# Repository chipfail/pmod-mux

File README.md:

# MUX PMOD Hardware
MUX PMOD Hardware

[Digikey Cart for 10 boards](https://www.digikey.com/short/pm0rpt)

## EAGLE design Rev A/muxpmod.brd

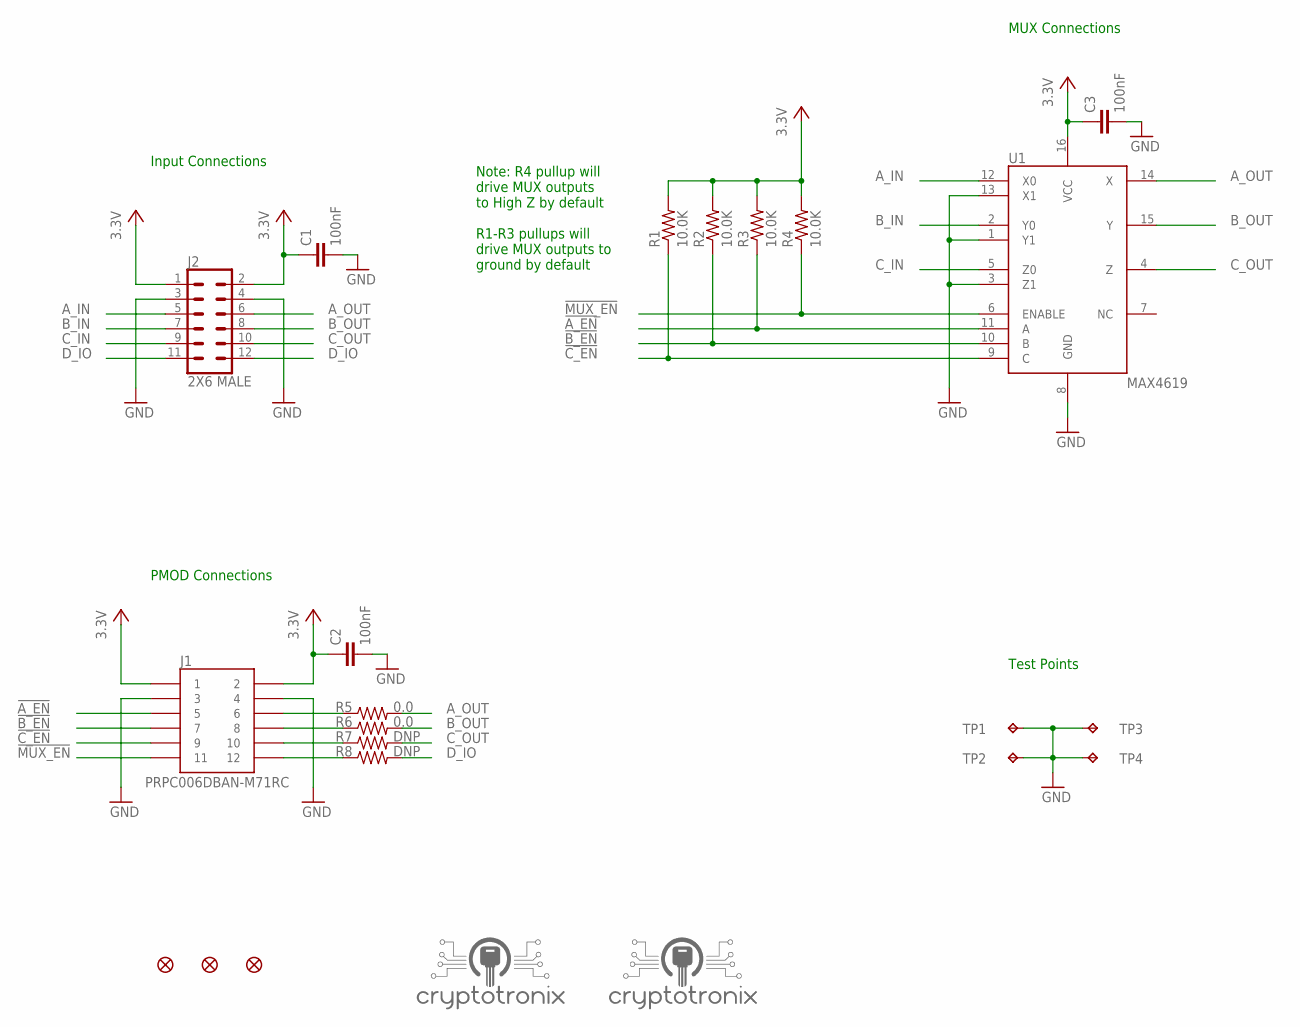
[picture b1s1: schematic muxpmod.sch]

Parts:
C1, C2, C3: 100nF; C0603
FD1, FD2, FD3: FIDUCIALUFIDUCIAL; MICRO-FIDUCIAL
J1: PRPC006DBAN-M71RC
J2: 2X6 MALE; 2X6
LOGO1, LOGO2: CRYPTOTRONIX_LOGO_S
R1, R2, R3, R4: 10.0K; R0603
R5, R6: 0.0; R0603
R7, R8: DNP; R0603
TP1, TP2, TP3, TP4: TEST-POINT-SM; 5015
U1: MAX4619; 16SOIC

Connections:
0V: C1.2, C2.2, C3.2, J1.3, J1.4, J2.3, J2.4, TP1.1, TP2.1, TP3.1, TP4.1, U1.1 (Y1), U1.3 (Z1), U1.8 (GND), U1.13 (X1)
3.3V: C1.1, C2.1, C3.1, J1.1, J1.2, J2.1, J2.2, R1.2, R2.2, R3.2, R4.2, U1.16 (VCC)
!A_EN: J1.5, R3.1, U1.11 (A)
!B_EN: J1.7, R2.1, U1.10 (B)
!C_EN: J1.9, R1.1, U1.9 (C)
!MUX_EN: J1.11, R4.1, U1.6 (ENABLE)
A_IN: J2.5, U1.12 (X0)
A_OUT: J2.6, R5.2, U1.14 (X)
B_IN: J2.7, U1.2 (Y0)
B_OUT: J2.8, R6.2, U1.15 (Y)
C_IN: J2.9, U1.5 (Z0)
C_OUT: J2.10, R7.2, U1.4 (Z)
D_IO: J2.11, J2.12, R8.2
unnamed: J1.6, R5.1
unnamed: J1.8, R6.1
unnamed: J1.10, R7.1
unnamed: J1.12, R8.1

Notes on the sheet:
PMOD Connections
MUX Connections
Note: R4 pullup will drive MUX outputs to High Z by default R1-R3 pullups will drive MUX outputs to ground by default
Test Points
Input Connections

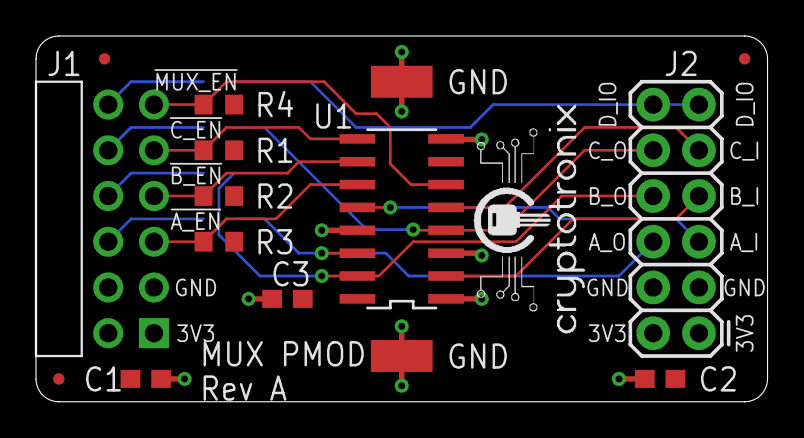
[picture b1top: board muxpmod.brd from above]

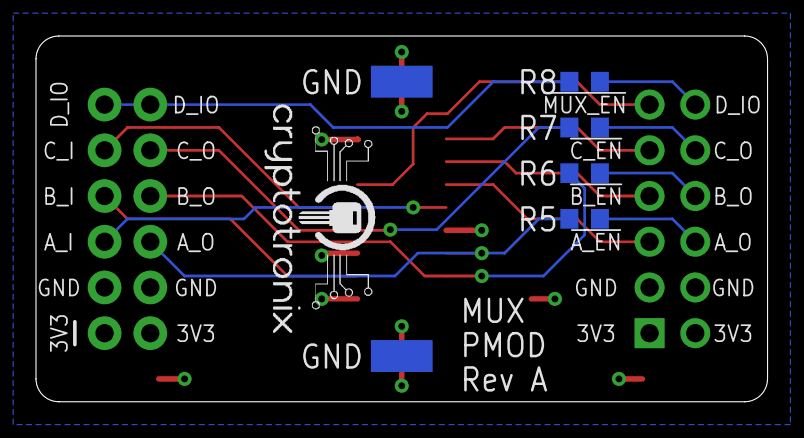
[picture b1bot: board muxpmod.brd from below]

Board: 2 copper layers, 40.6 x 20.3 mm, 23 parts (7 on the bottom side), 17 nets.

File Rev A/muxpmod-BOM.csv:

Qty;Value;Device;Package;Parts;Description;MAN-PART_NUM;MANUFACTURER
2;0;R-US_R0603;R0603;R5, R6;RESISTOR, American symbol;RMCF0603ZT0R00;Stackpole Electronics Inc
4;10.0K;R-US_R0603;R0603;R1, R2, R3, R4;RESISTOR, American symbol;RNCP0603FTD10K0;Stackpole Electronics Inc
3;100nF;C-EUC0603;C0603;C1, C2, C3;CAPACITOR, European symbol;CL10B104KB8NNNC;Samsung Electro-Mechanics
1;2X6 MALE;CONN_06X2PTH_FEMALE;2X6;J2;Multi connection point. Often used as Generic Header-pin footprint for 0.1 inch spaced/style header connections;PRPC006DAAN-RC;Sullins Connector Solutions
2;DNP;R-US_R0603;R0603;R7, R8;RESISTOR, American symbol;DNP;DNP
1;MAX4619;MAX4619;16SOIC;U1;IC MUX/SW TRIPLE LV SPDT 16-SOIC;MAX4619CSE+;Maxim Integrated
1;PRPC006DBAN-M71RC;PRPC006DBAN-M71RC;PRPC006DBAN-M71RC;J1;Connector Header Through Hole;PRPC006DBAN-M71RC;Sullins
4;TEST-POINT-SM;TEST-POINT-SM;5015;TP1, TP2, TP3, TP4;Various Test Points;5015;KEYSTONE

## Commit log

2019-06-13 Updating digikey cart

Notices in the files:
parts and their libraries:
SparkFun-Connectors: Licensing: Creative Commons ShareAlike 4.0 International - https://creativecommons.org/licenses/by-sa/4.0
